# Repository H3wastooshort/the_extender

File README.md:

# The Extender
Modern phones suck in theor own unique way, don't they?
Hard-to-replace or -expand lithium cells, no expandable storage, and worst of all: no headphone jack!

This projects aims to fix some of those flaws by
combining a powerbank, USB hub, USB audio, and RP2040 IC into one very cursed PCB.

## Working Principle
5V power and battery charging is handled by an IP5310 powerbank IC.

The PCB connects to a phone via a low-profile 90° USB Type C cable (either [DIY](/cable) or [bought](https://de.aliexpress.com/item/1005005371248824.html)).
Once connected, the RP2040 turns on 5V power, then uses the FUSB302 to tell the phone via USB Power Delivery,
that it should keep charging while also switching into USB Data Host mode.

The phone then connects to the CH334F USB Hub IC, which in turn connects to several things:
 * a USB 3.0 socket for a USB Stick which is used to expand the internal storage,
 * the HS-100B USB audio IC, (only powered on when headphones are connected)
 * the RP2040 for HID volume and playback control aswell as FW Updates,
 * and an external USB 2.0 socket for whatever you desire.

## 3D-printable case
WIP

## schematic POIs

### HS-100B Audio IC
 * The Audio IC circuit is based on a low-resolution image of a reference design i found online.
 * 5V Power to the IC gets cut va a MOSFET when the headphones are disconnected. An RC circuit prevents loose plugs from causing issues. (Turns off about 1 second after unplugging)
 * The datasheet is quite sparse
 * The EEPROM data lines are connected to the RP2040, so that it can emulate the EEPROM in the future. This is not requred.

### IP5310 power-bank IC
 * I2C variant is unobtainium
 * MOSFET between VOUT and rest of system, so that power to phone and other components can be controlled
   even though VOUT can't.
 * if needed, a solder jumper can be cut and shottky diode put in place to prevent current flowing back into the IC
 * KEY pin connected to RP2040. might be needed, i don't know, should turn on when detecting a load
 * D+ and D- not connected because there is very little space. the CC lines should suffice

### CH334F
 * clock line can be grounded to use internal OSC, but this is discouraged in its datasheet.
   RP2040 is to provide a better clock once programmed.
 * 

### RP2040
 * main purpose is to communicate via USB C PD
 * might supply clock for hub
 * might be used to emulate EEPROMs for USB Hub and Audio

## more info

The [idea](/idea) directory has some partially outdated notes.

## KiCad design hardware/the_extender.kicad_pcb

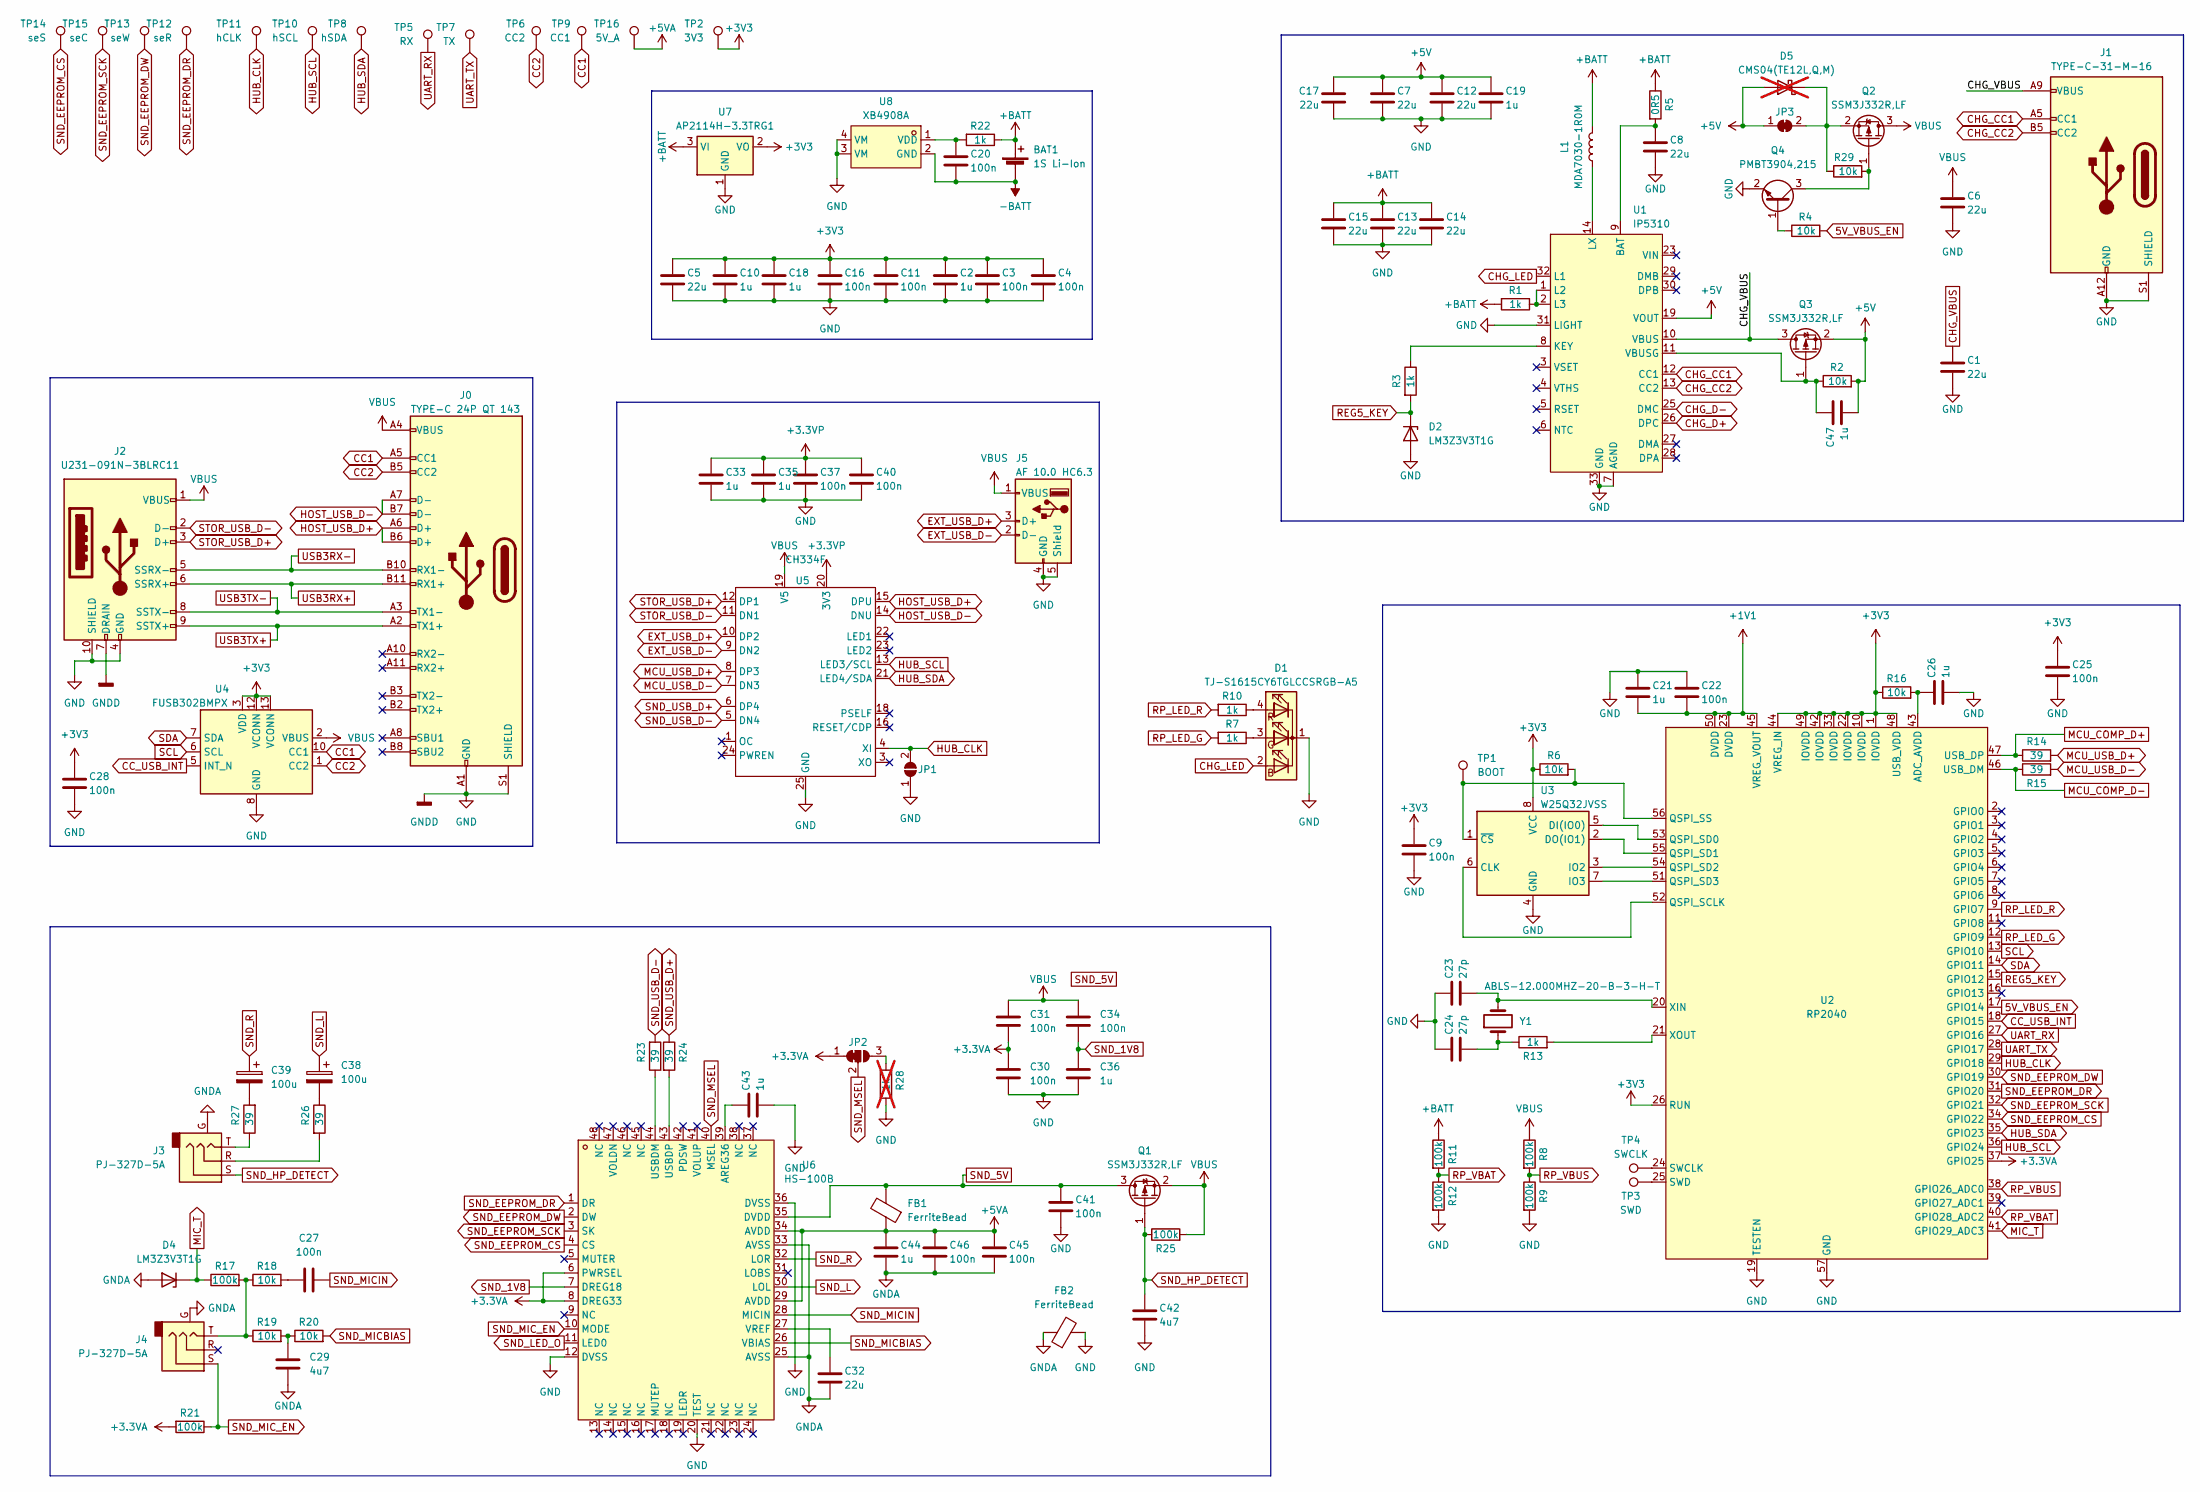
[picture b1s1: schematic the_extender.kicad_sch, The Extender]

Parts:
BAT1: 1S Li-Ion; PinHeader_1x02_P2.54mm_Vertical
C1, C5, C6, C7, C8, C12, C13, C14, C15, C17, C32: 22u; C_1206_3216Metric_Pad1.33x1.80mm_HandSolder; LCSC C12891
C2, C10, C18, C19, C21, C26, C33, C35, C36, C43, C44, C47: 1u; C_0805_2012Metric_Pad1.18x1.45mm_HandSolder; LCSC C116352
C3, C4, C9, C11, C16, C20, C22, C25, C27, C28, C30, C31, C34, C37, C40, C41, C45, C46: 100n; C_0805_2012Metric_Pad1.18x1.45mm_HandSolder; LCSC C1711
C23, C24: 27p; C_0805_2012Metric_Pad1.18x1.45mm_HandSolder; LCSC C525289
C29, C42: 4u7; C_0805_2012Metric_Pad1.18x1.45mm_HandSolder; LCSC C1779
C38, C39: 100u; C_1206_3216Metric_Pad1.33x1.80mm_HandSolder; LCSC C15008
D1: TJ-S1615CY6TGLCCSRGB-A5; LED-ARRAY-SMD_4P-L1.6-W1.5-BL-FD; LCSC C601684
D2, D4: LM3Z3V3T1G; D_SOD-323_HandSoldering; LCSC C46279
D5: CMS04(TE12L,Q,M); D_SOD-128; LCSC C603062; not fitted
FB1, FB2: FerriteBead; L_0805_2012Metric_Pad1.05x1.20mm_HandSolder; LCSC C394433
J0: TYPE-C 24P QT 143; TYPE-C-SMD_C9900025773; LCSC Part C5156605
J1: TYPE-C-31-M-16; LCSC C283541
J2: U231-091N-3BLRC11; USB-A-TH_XKB_U231-091N-XXX; LCSC Part C2880594
J3, J4: PJ-327D-5A; AUDIO-TH_PJ-327D-5A; LCSC Part C707229
J5: AF 10.0 HC6.3; USB-A-TH_AF-10.0-HC6.3; LCSC Part C456017
JP1: SolderJumper_2_Open; SolderJumper-2_P1.3mm_Open_TrianglePad1.0x1.5mm
JP2: SolderJumper_3_Bridged12; SolderJumper-3_P1.3mm_Bridged12_Pad1.0x1.5mm_NumberLabels
JP3: SolderJumper_2_Bridged; SolderJumper-2_P1.3mm_Bridged_Pad1.0x1.5mm
L1: MDA7030-1R0M; IND-SMD_L7.1-W6.6; LCSC Part C2847480
Q1, Q2, Q3: SSM3J332R,LF; SOT-23_Handsoldering; LCSC C146367
Q4: PMBT3904,215; SOT-23_Handsoldering; LCSC C8667
R1, R3, R7, R10, R13, R22: 1k; R_0805_2012Metric_Pad1.20x1.40mm_HandSolder; LCSC C110774
R2, R4, R6, R16, R18, R19, R20, R29: 10k; R_0805_2012Metric_Pad1.20x1.40mm_HandSolder; LCSC C217770
R5: 0R5; R_0805_2012Metric_Pad1.20x1.40mm_HandSolder; LCSC C218422
R8, R9, R11, R12, R17, R21, R25: 100k; R_0805_2012Metric_Pad1.20x1.40mm_HandSolder; LCSC C217765
R14, R15, R23, R24, R26, R27: 39; R_0805_2012Metric_Pad1.20x1.40mm_HandSolder; LCSC C2828722
R28: 1k; R_0805_2012Metric_Pad1.20x1.40mm_HandSolder; LCSC C110774; not fitted
TP1: BOOT; TestPoint_Pad_D2.0mm
TP2: 3V3; TestPoint_Pad_D2.0mm
TP3: SWD; TestPoint_Pad_D2.0mm
TP4: SWCLK; TestPoint_Pad_D2.0mm
TP5: RX; TestPoint_Pad_D1.0mm
TP6: CC2; TestPoint_Pad_D1.0mm
TP7: TX; TestPoint_Pad_D2.0mm
TP8: hSDA; TestPoint_Pad_D1.0mm
TP9: CC1; TestPoint_Pad_D1.0mm
TP10: hSCL; TestPoint_Pad_D1.0mm
TP11: hCLK; TestPoint_Pad_D1.0mm
TP12: seR; TestPoint_Pad_D2.0mm
TP13: seW; TestPoint_Pad_D2.0mm
TP14: seS; TestPoint_Pad_D2.0mm
TP15: seC; TestPoint_Pad_D2.0mm
TP16: 5V_A; TestPoint_Pad_D2.0mm
U1: IP5310; QFN-32_L5.0-W5.0-P0.50-BL-EP3.4; LCSC Part C191176
U2: RP2040; LQFN-56_L7.0-W7.0-P0.4-EP; LCSC Part C2040
U3: W25Q32JVSS; SOIC-8_5.23x5.23mm_P1.27mm; LCSC C179173
U4: FUSB302BMPX; WQFN-14-1EP_2.5x2.5mm_P0.5mm_EP1.45x1.45mm; LCSC Part C442699
U5: CH334F; QFN-24-1EP_4x4mm_P0.5mm_EP2.6x2.6mm; LCSC Part C5187527
U6: HS-100B; LQFP-48_7x7mm_P0.5mm; LCSC Part C371351
U7: AP2114H-3.3TRG1; SOT-223-3_TabPin2; LCSC C150716
U8: XB4908A; ESN-4_L2.8-W2.3-LS3.7-BL; LCSC Part C2998740
Y1: ABLS-12.000MHZ-20-B-3-H-T; Crystal_SMD_7050-2Pin_7.0x5.0mm_HandSoldering; LCSC C1985323

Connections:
5V_VBUS_EN: R4.2, U2.17 (GPIO14)
+1V1: C21.2, C22.2, U2.23 (DVDD), U2.45 (VREG_VOUT), U2.50 (DVDD)
+3.3VA: C30.2, C31.1, JP2.1 (A), R21.2, U2.37 (GPIO25), U6.6 (PWRSEL), U6.8 (DREG33)
+3.3VP: C33.1, C35.1, C37.1, C40.1, U5.20 (3V3)
+3V3: C2.1, C3.1, C4.1, C5.1, C9.1, C10.1, C11.1, C16.1, C18.1, C25.1, C28.1, R6.1, R16.1, TP2.1, U2.1 (IOVDD), U2.10 (IOVDD), U2.22 (IOVDD), U2.26 (RUN), U2.33 (IOVDD), U2.42 (IOVDD), U2.44 (VREG_IN), U2.48 (USB_VDD), U2.49 (IOVDD), U3.8 (VCC), U4.3 (VDD), U4.4 (VDD), U4.12 (VCONN), U4.13 (VCONN), U7.2 (VO)
+5V: C7.1, C12.1, C17.1, C19.1, C47.2, D5.2 (A), JP3.1 (A), Q3.2 (S), R2.2, U1.19 (VOUT), U1.20 (VOUT), U1.21 (VOUT), U1.22 (VOUT)
+5VA: C44.1, C45.1, C46.1, FB1.1, TP16.1, U6.29 (AVDD), U6.34 (AVDD)
+BATT: BAT1.1 (+), C13.1, C14.1, C15.1, L1.2, R1.2, R5.1, R11.1, R22.1, U7.3 (VI)
-BATT: BAT1.2 (-), C20.2, U8.2 (GND)
CC1: J0.A5 (CC1), TP9.1, U4.10 (CC1), U4.11 (CC1)
CC2: J0.B5 (CC2), TP6.1, U4.1 (CC2), U4.14 (CC2)
CC_USB_INT: U2.18 (GPIO15), U4.5 (INT_N)
CHG_CC1: J1.A5 (CC1), U1.12 (CC1)
CHG_CC2: J1.B5 (CC2), U1.13 (CC2)
CHG_D+: U1.26 (DPC)
CHG_D-: U1.25 (DMC)
CHG_LED: D1.2 (BA), U1.32 (L1)
CHG_VBUS: C1.1, J1.A9 (VBUS), J1.B9 (VBUS), Q3.3 (D), U1.10 (VBUS)
EXT_USB_D+: J5.3 (D+), U5.10 (DP2)
EXT_USB_D-: J5.2 (D-), U5.9 (DN2)
GND: C1.2, C2.2, C3.2, C4.2, C5.2, C6.2, C7.2, C8.2, C9.2, C10.2, C11.2, C12.2, C13.2, C14.2, C15.2, C16.2, C17.2, C18.2, C19.2, C21.1, C22.1, C23.1, C24.1, C25.2, C26.2, C28.2, C30.1, C33.2, C35.2, C36.1, C37.2, C40.2, C41.2, C42.2, C43.2, D1.1 (K), D2.2 (A), FB2.2, J0.A1 (GND), J0.A12 (GND), J0.B1 (GND), J0.B12 (GND), J0.S1 (SHIELD), J1.A12 (GND), J1.B12 (GND), J1.S1 (SHIELD), J2.4 (GND), J2.7 (DRAIN), J2.10 (SHIELD), J5.4 (GND), J5.5 (Shield), JP1.1 (A), Q4.2 (E), R9.2, R12.2, R28.1, U1.7 (AGND), U1.31 (LIGHT), U1.33 (GND), U2.19 (TESTEN), U2.57 (GND), U3.4 (GND), U4.8 (GND), U4.9 (GND), U4.15 (GND), U5.25 (GND), U6.12 (DVSS), U6.20 (TEST), U6.36 (DVSS), U7.1 (GND), U8.3 (VM), U8.4 (VM)
GNDA: C29.1, C32.2, C44.2, C45.2, C46.2, D4.2 (A), FB2.1, J3.G, J4.G, U6.25 (AVSS), U6.33 (AVSS)
HOST_USB_D+: J0.A6 (D+), J0.B6 (D+), U5.15 (DPU)
HOST_USB_D-: J0.A7 (D-), J0.B7 (D-), U5.14 (DNU)
HUB_CLK: JP1.2 (B), TP11.1, U2.29 (GPIO18), U5.4 (XI)
HUB_SCL: TP10.1, U2.36 (GPIO24), U5.13 (LED3/SCL)
HUB_SDA: TP8.1, U2.35 (GPIO23), U5.21 (LED4/SDA)
MCU_COMP_D+: R14.1, U2.47 (USB_DP)
MCU_COMP_D-: R15.1, U2.46 (USB_DM)
MCU_USB_D+: R14.2, U5.8 (DP3)
MCU_USB_D-: R15.2, U5.7 (DN3)
MIC_T: D4.1 (K), R17.1, U2.41 (GPIO29_ADC3)
unnamed: C24.2, R13.1, Y1.1
unnamed: C27.1, R18.2
unnamed: C29.2, R19.2, R20.1
unnamed: C38.2, R26.1
unnamed: C39.2, R27.2
unnamed: D1.3 (GA), R7.1
unnamed: D1.4 (RA), R10.1
unnamed: D5.1 (K), JP3.2 (B), Q2.2 (S), R29.1
unnamed: J3.R, R26.2
unnamed: J3.T, R27.1
unnamed: J4.T, R17.2, R18.1, R19.1
unnamed: JP2.3 (B), R28.2
unnamed: L1.1, U1.14 (LX), U1.15 (LX), U1.16 (LX), U1.17 (LX), U1.18 (LX)
unnamed: Q2.1 (G), Q4.3 (C), R29.2
unnamed: C47.1, Q3.1 (G), R2.1, U1.11 (VBUSG)
unnamed: Q4.1 (B), R4.1
unnamed: C8.1, R5.2, U1.9 (BAT)
unnamed: R3.1, U1.8 (KEY)
unnamed: R1.1, U1.1 (L2), U1.2 (L3)
unnamed: C26.1, R16.2, U2.43 (ADC_AVDD)
unnamed: U2.52 (QSPI_SCLK), U3.6 (CLK)
unnamed: U2.53 (QSPI_SD0), U3.5 (DI(IO0))
unnamed: U2.55 (QSPI_SD1), U3.2 (DO(IO1))
unnamed: U2.54 (QSPI_SD2), U3.3 (IO2)
unnamed: U2.51 (QSPI_SD3), U3.7 (IO3)
unnamed: R6.2, TP1.1, U2.56 (QSPI_SS), U3.1 (~CS)
unnamed: TP4.1, U2.24 (SWCLK)
unnamed: TP3.1, U2.25 (SWD)
unnamed: C23.2, U2.20 (XIN), Y1.2
unnamed: R13.2, U2.21 (XOUT)
unnamed: C43.1, U6.39 (AREG36)
unnamed: R23.1, U6.44 (USBDM)
unnamed: R24.2, U6.43 (USBDP)
unnamed: C32.1, U6.27 (VREF)
unnamed: C20.1, R22.2, U8.1 (VDD)
REG5_KEY: D2.1 (K), R3.2, U2.15 (GPIO12)
RP_LED_G: R7.2, U2.12 (GPIO9)
RP_LED_R: R10.2, U2.9 (GPIO7)
RP_VBAT: R11.2, R12.1, U2.40 (GPIO28_ADC2)
RP_VBUS: R8.2, R9.1, U2.38 (GPIO26_ADC0)
SCL: U2.13 (GPIO10), U4.6 (SCL)
SDA: U2.14 (GPIO11), U4.7 (SDA)
SND_1V8: C34.1, C36.2, U6.7 (DREG18)
SND_5V: C41.1, FB1.2, Q1.3 (D), U6.35 (DVDD)
SND_EEPROM_CS: TP14.1, U2.34 (GPIO22), U6.4 (CS)
SND_EEPROM_DR: TP12.1, U2.31 (GPIO20), U6.1 (DR)
SND_EEPROM_DW: TP13.1, U2.30 (GPIO19), U6.2 (DW)
SND_EEPROM_SCK: TP15.1, U2.32 (GPIO21), U6.3 (SK)
SND_HP_DETECT: C42.1, J3.S, Q1.1 (G), R25.1
SND_L: C38.1, U6.30 (LOL)
SND_LED_O: U6.11 (LED0)
SND_MICBIAS: R20.2, U6.26 (VBIAS)
SND_MICIN: C27.2, U6.28 (MICIN)
SND_MIC_EN: J4.S, R21.1, U6.10 (MODE)
SND_MSEL: JP2.2 (C), U6.40 (MSEL)
SND_R: C39.1, U6.32 (LOR)
SND_USB_D+: R24.1, U5.6 (DP4)
SND_USB_D-: R23.2, U5.5 (DN4)
STOR_USB_D+: J2.3 (D+), U5.12 (DP1)
STOR_USB_D-: J2.2 (D-), U5.11 (DN1)
UART_RX: TP5.1, U2.27 (GPIO16)
UART_TX: TP7.1, U2.28 (GPIO17)
USB3RX+: J0.B11 (RX1+), J2.6 (SSRX+)
USB3RX-: J0.B10 (RX1-), J2.5 (SSRX-)
USB3TX+: J0.A2 (TX1+), J2.9 (SSTX+)
USB3TX-: J0.A3 (TX1-), J2.8 (SSTX-)
VBUS: C6.1, C31.2, C34.2, J0.A4 (VBUS), J0.A9 (VBUS), J0.B4 (VBUS), J0.B9 (VBUS), J2.1 (VBUS), J5.1 (VBUS), Q1.2 (S), Q2.3 (D), R8.1, R25.2, U4.2 (VBUS), U5.19 (V5)

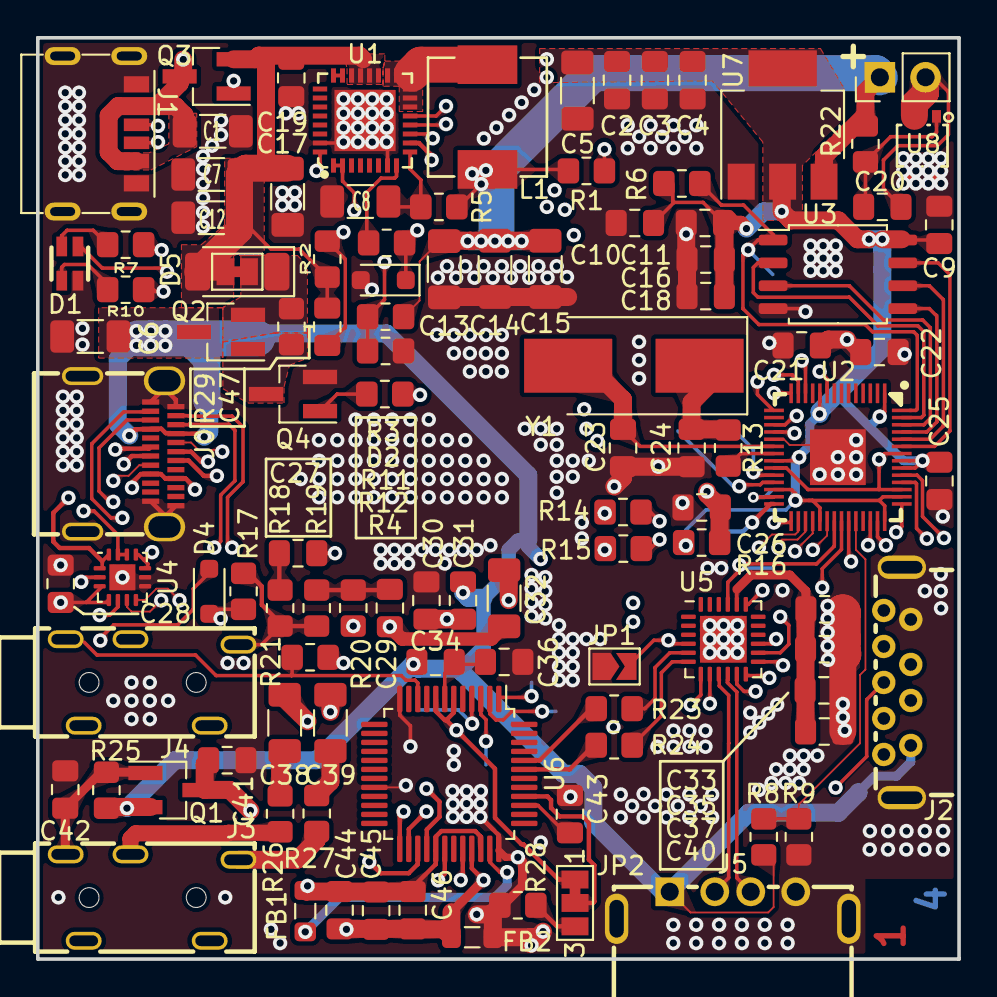
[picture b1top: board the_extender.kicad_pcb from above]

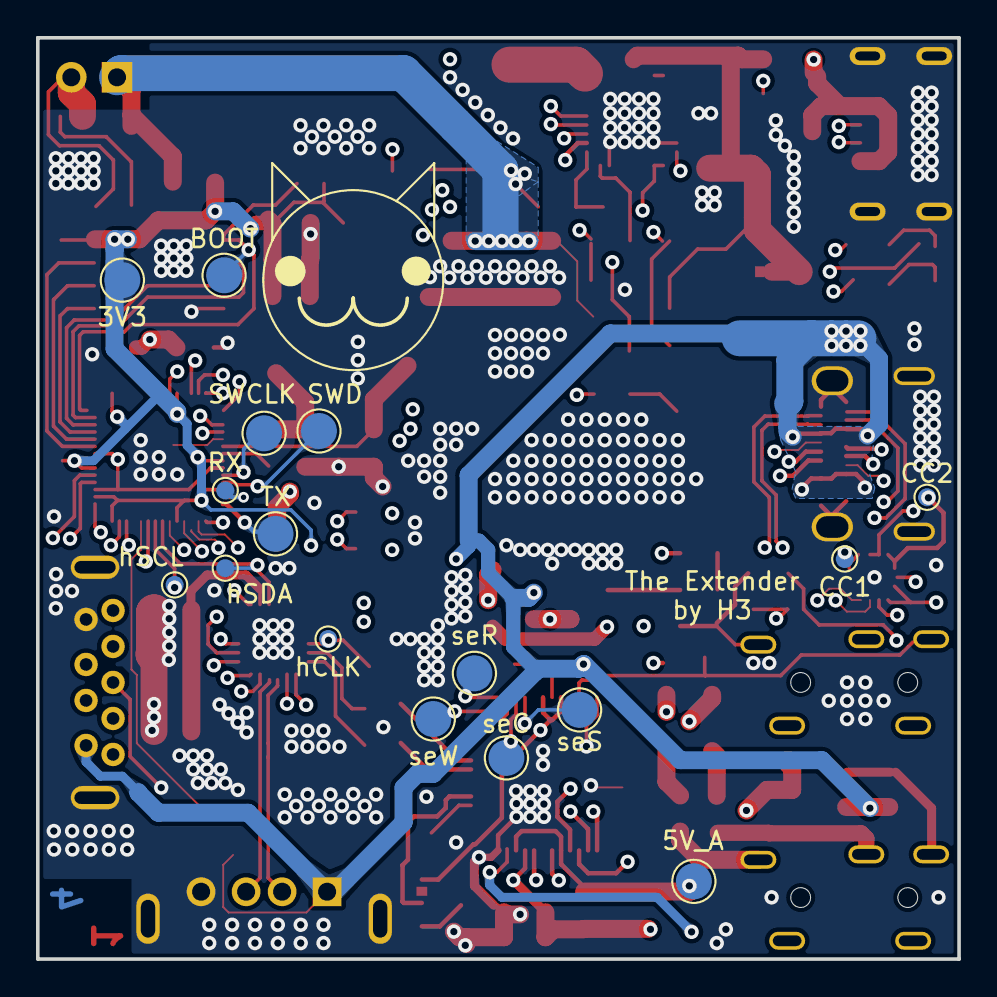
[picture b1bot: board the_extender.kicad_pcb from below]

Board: 4 copper layers, 51.2 x 51.2 mm, 122 parts (16 on the bottom side), 96 nets.

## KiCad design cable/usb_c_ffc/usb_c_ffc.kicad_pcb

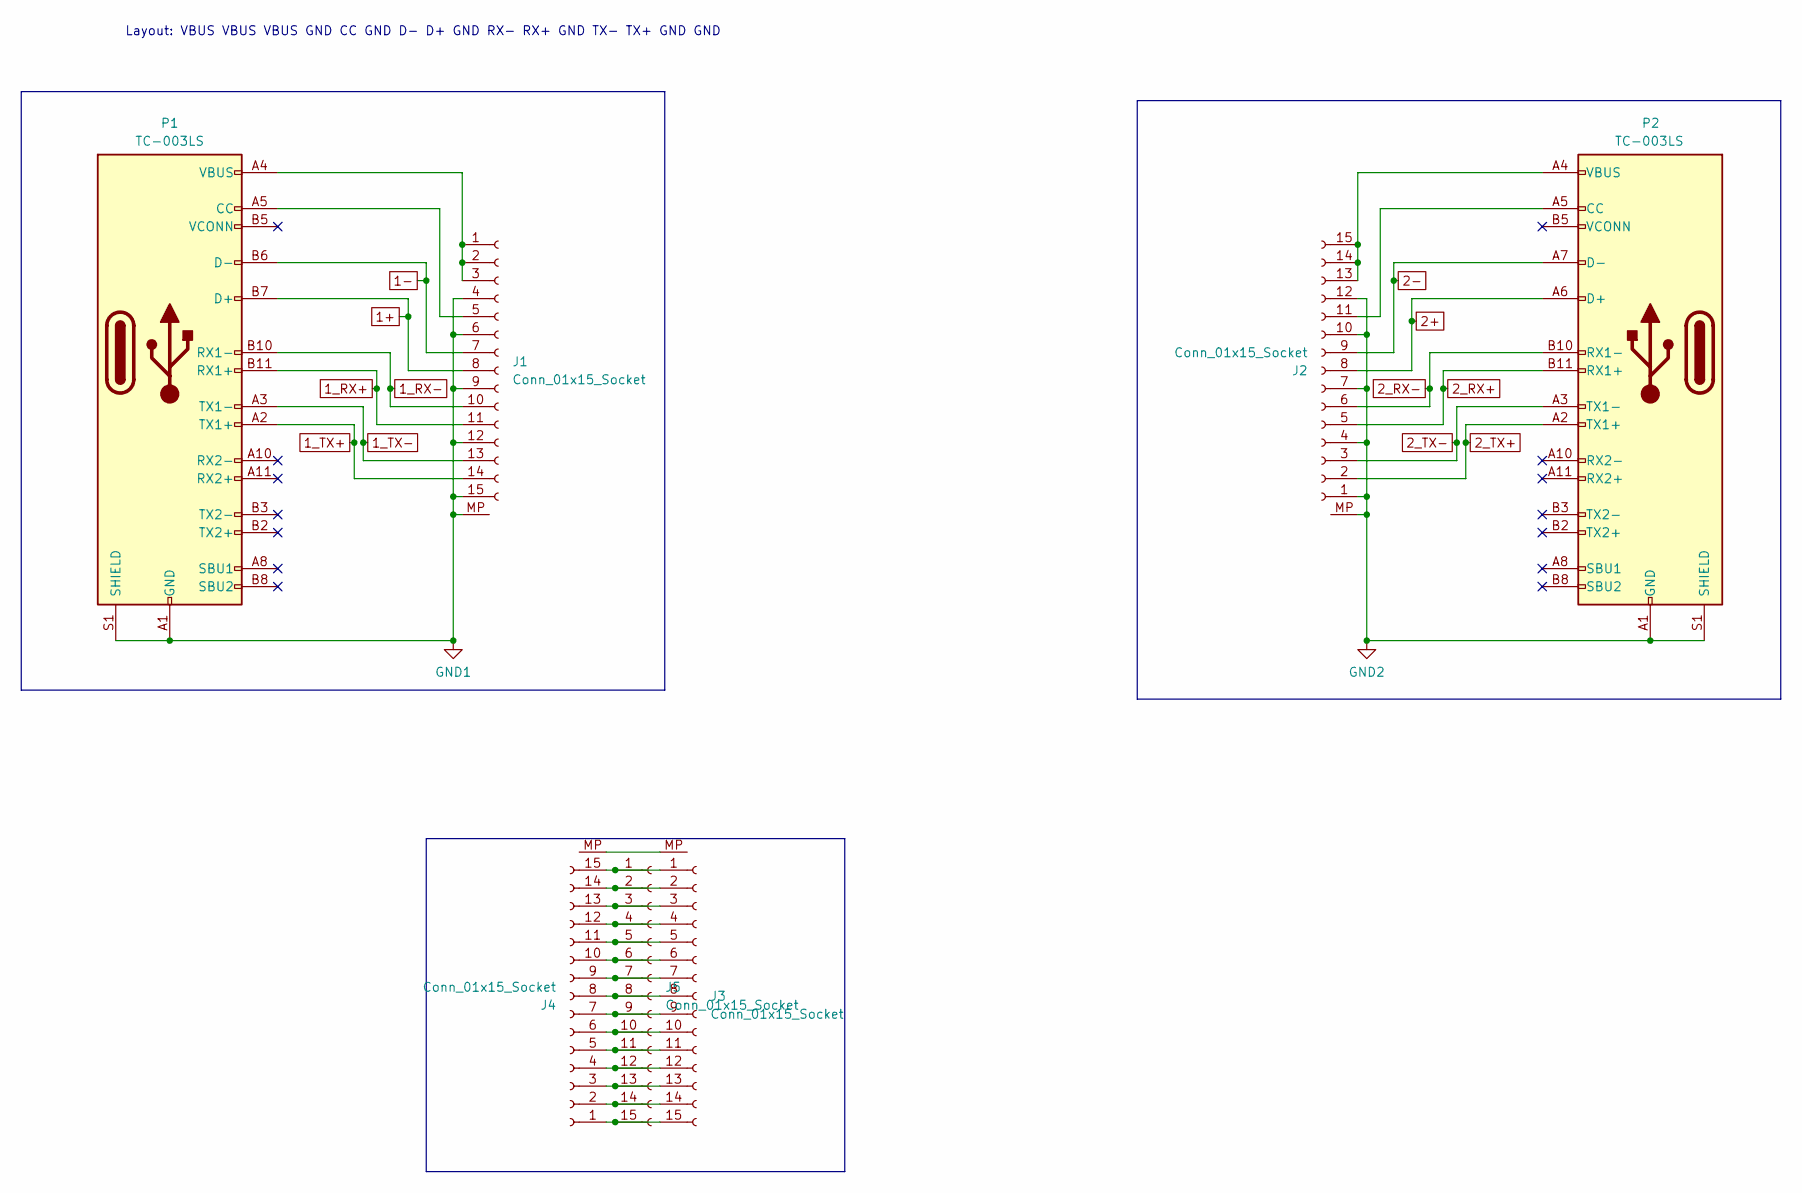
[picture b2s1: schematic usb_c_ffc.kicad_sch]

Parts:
J1, J2, J3, J4: Conn_01x15_Socket; Molex_200528-0150_1x15-1MP_P1.00mm_Horizontal
J5: Conn_01x15_Socket; PinHeader_1x15_P2.54mm_Vertical
P1, P2: TC-003LS

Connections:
1+: J1.8, P1.B7 (D+)
1-: J1.7, P1.B6 (D-)
1_RX+: J1.11, P1.B11 (RX1+)
1_RX-: J1.10, P1.B10 (RX1-)
1_TX+: J1.14, P1.A2 (TX1+)
1_TX-: J1.13, P1.A3 (TX1-)
2+: J2.8, P2.A6 (D+)
2-: J2.9, P2.A7 (D-)
2_RX+: J2.5, P2.B11 (RX1+)
2_RX-: J2.6, P2.B10 (RX1-)
2_TX+: J2.2, P2.A2 (TX1+)
2_TX-: J2.3, P2.A3 (TX1-)
GND1: J1.4, J1.6, J1.9, J1.12, J1.15, J1.MP, P1.A1 (GND), P1.A12 (GND), P1.B1 (GND), P1.B12 (GND), P1.S1 (SHIELD)
GND2: J2.1, J2.4, J2.7, J2.10, J2.12, J2.MP, P2.A1 (GND), P2.A12 (GND), P2.B1 (GND), P2.B12 (GND), P2.S1 (SHIELD)
unnamed: J1.1, J1.2, J1.3, P1.A4 (VBUS), P1.A9 (VBUS), P1.B4 (VBUS), P1.B9 (VBUS)
unnamed: J1.5, P1.A5 (CC)
unnamed: J2.11, P2.A5 (CC)
unnamed: J2.13, J2.14, J2.15, P2.A4 (VBUS), P2.A9 (VBUS), P2.B4 (VBUS), P2.B9 (VBUS)
unnamed: J3.MP, J4.MP
unnamed: J3.1, J4.15, J5.1
unnamed: J3.2, J4.14, J5.2
unnamed: J3.3, J4.13, J5.3
unnamed: J3.4, J4.12, J5.4
unnamed: J3.5, J4.11, J5.5
unnamed: J3.6, J4.10, J5.6
unnamed: J3.7, J4.9, J5.7
unnamed: J3.8, J4.8, J5.8
unnamed: J3.9, J4.7, J5.9
unnamed: J3.10, J4.6, J5.10
unnamed: J3.11, J4.5, J5.11
unnamed: J3.12, J4.4, J5.12
unnamed: J3.13, J4.3, J5.13
unnamed: J3.14, J4.2, J5.14
unnamed: J3.15, J4.1, J5.15

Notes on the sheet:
Layout: VBUS VBUS VBUS GND CC GND D- D+ GND RX- RX+ GND TX- TX+ GND GND

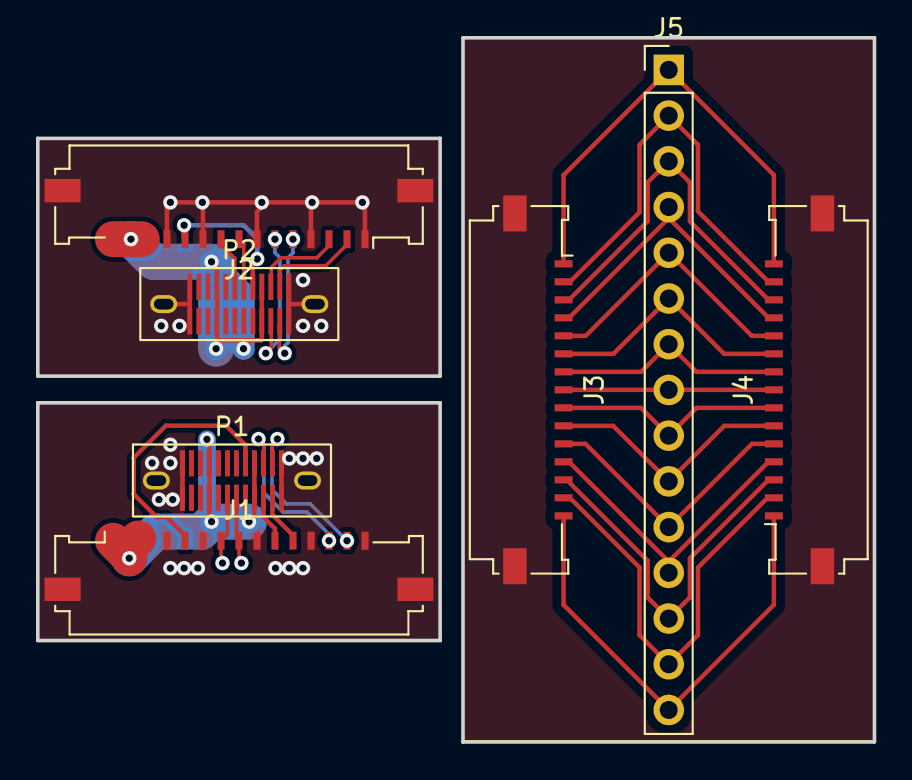
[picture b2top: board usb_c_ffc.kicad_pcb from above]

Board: 2 copper layers, 46.5 x 39.1 mm, 7 parts (0 on the bottom side), 34 nets.

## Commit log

2023-12-17 worked on schematic
2023-12-17 some more caps n stuff
2023-12-20 did things
2023-12-21 did things, tried to arrange components
2023-12-21 trying to layout board
2023-12-22 got most stuff stuffed onto the PCB
2023-12-22 flip layers so power is routed on heavier traces
2023-12-22 done some more stuff
2023-12-23 i might have finished routing signals
2023-12-23 ground planes in
2023-12-23 added some missing connections
2023-12-23 fix bugs
2023-12-23 use default footprints
2023-12-23 add missing trace, fix bugs
2023-12-25 added even more connections i forgot
2023-12-25 stuff
2023-12-25 automatic cleanup
2023-12-25 manual cleanup
2023-12-25 better groundplane for pb chip
2023-12-25 improve groundplanes
2023-12-26 add lcsc mappings
2023-12-26 3d models
2023-12-26 DRC stuff
2023-12-27 reread IP5310 datasheet, better groundplanes, other
2023-12-27 actually fix U6 footprint
2023-12-28 fix clearances
2023-12-28 more clearance and ground stuff
2023-12-28 auto cleanup
2023-12-28 part of 4ac6dc7472c68df24555d1d21356125b5eaefc59
2023-12-28 dont need VBUS on FUSB302
    that just kills them sometimes
2023-12-28 notes
2023-12-28 rp2040 boot TP
2023-12-28 update to kicad 7
2023-12-28 stuff
    clearances, remove unnesaccary components, etc
2023-12-28 program flow
2023-12-28 added layer indicator
2023-12-28 switch to new connector, part a
2023-12-28 new connector, part 2
2023-12-28 geographical reannotate
2023-12-29 added CC test pads
2023-12-30 debug TX pad
2023-12-30 usb c stuff idea
2023-12-30 todo
2023-12-30 now i know
2023-12-31 Imported code from @CRImier /AltmodeFriend
    https://github.com/CRImier/AltmodeFriend/blob/main/main.py
2023-12-31 strip sink stuff
2023-12-31 idk if that works
2023-12-31 take out more sink stuff
    this is nice code, but the extender should never be a sink and i want to keep this as short as possible. sorry
2023-12-31 sketch
2023-12-31 freq
2024-01-01 added USB C flat-flex cable adapters
2024-01-02 giving up on eeprom emulation, not enough board space
2024-01-03 cable pcb panel
2024-01-03 better HP detection
2024-01-04 applied changes to PCB
2024-01-04 add EEPROM emulation back
2024-01-04 amend todo
2024-01-04 silkscreen overlap, geo reannotate, teardrops
2024-01-04 oops, forgot to refill zones
2024-01-04 move cable files
2024-01-04 protect RP2040 from 3V6
2024-01-05 switching to IP5306, step 1: schematic
2024-01-05 bruh
2024-01-05 oh yeah, the 5k1 resistors
2024-01-05 switching to IP5306, step 2: PCB
2024-01-05 had to move the IC a little
2024-01-05 fixup silkscreen, voltage limits, etc
2024-01-05 fix U6 being detected as "additional footprint"
2024-01-07 fix me fucking up footprints
2024-01-07 use mousebites on cable instead
2024-01-07 ah whatever
    i will just go with 3 seperate PCBs. its actually cheaper that way
2024-01-07 split
2024-01-07 add debounce circuit
2024-01-07 gitignore
2024-01-07 teardrops
2024-01-10 finalizing design
2024-01-10 still not quite done
2024-01-11 reconnect VBUS to FUSB302
    i think its needed for the pullups
2024-01-11 update LCSC parts
2024-01-11 add bom conversion script
2024-01-11 switch 3v3 footprint, fixup stuff
2024-01-11 forgot to change id
2024-01-13 trying to do a customizable case in scad
2024-01-17 switch to cheaper and smaller usb hub, part 1
2024-01-17 switch usb hub, part 2: PCB
2024-01-17 board optimizations
2024-01-17 small fixes
2024-01-17 Switch to linear LDO Regulator to decrease cost
    might also improve ADC accuracy...
2024-01-17 slightly improved thermal fill
2024-01-17 removed back s.mask from some in-pad vias
2024-01-17 oops
2024-01-17 auto-cleanup
2024-01-17 oh, this belongs to an earlier commit
2024-01-18 update LCSC parts
    i always forgot to update the schematic :facepalm:
2024-01-18 [bom script] count components
2024-01-18 fix lcsc parts
2024-01-18 fix bom excludes
2024-01-18 change inductor and fix things
2024-01-18 geo reannotate
2024-01-21 fix some more in-pad-vias
2024-01-26 space comonents out more in audio section
2024-01-26 add teardrops
2024-01-26 forgot to refill zones. oops
2024-01-26 fix testpad labels
2024-01-26 fix LCSC part numbers
2024-01-26 ground area
2024-01-26 lcsc ids
2024-02-09 added headphone plug-in detection, other stuff
2024-02-09 fix USB3 footprint
2024-02-09 silkscreen slightly more readable
2024-02-09 silkscreen
2024-02-15 add 5V solderjumper
2024-02-15 remove teardrops again
2024-02-15 add diode mosfet
2024-02-15 ok, just a regular diode then...
2024-02-15 fix DRC errors
2024-02-15 move silk txt
2024-02-15 switche diode FP, shuffle silk around
2024-02-15 more silk stuff
2024-02-15 auto-cleanup and taerdrops
2024-02-16 move USB3 cable to seperate folder
2024-02-16 added nice little USB2 cable variant
2024-02-16 hide too small silkscreen text
2024-02-16 change routing
2024-02-17 switching back to IP5310, step 1: schematic
    Switching back to IP5310 with different 5V enable circuit
    This has several advantages:
    * being able to output power via the charging port
    * being sure the 5V power will be able to be switched off
    * 3A-capable supply
    Disadvantage:
2024-02-17 npn selection
2024-02-17 rm teardrops
2024-02-17 kinda did it
2024-02-17 add way to measure VBUS
2024-02-17 silk slightly less horrible
2024-02-18 silkscreen schubsen
2024-02-18 add Li-Ion protection circuit
2024-02-18 cell protection fixes
2024-02-18 reinforce BATT- with solder, small fixes
2024-02-18 lcsc
2024-02-18 change RGB LED
    old one was out of stock
2024-02-18 led 3d model
2024-02-22 improved thermal areas, trace routing, other
2024-02-22 gnd fix
2024-02-22 auto clean and fix teardrops
2024-02-22 i forgot to rebuild zones
2024-02-22 stop DRC from complaining
2024-02-22 why did the LCSC part numbers not transfer?
2024-02-22 slight routing changes
2024-03-01 add more TPs, opem SolderJumper
2024-03-01 move TPs
2024-03-01 fix DRC error
2024-03-01 refresh teardrops
2024-03-01 Revert "Merge branch 'main' of https://github.com/H3wastooshort/the_extender"
    This reverts commit db196a6756d0956c3d1d8ec495d7e3985efbbc7b, reversing
    changes made to 4fcd2dbd9a370267836c4c164a7f38c8495f449e.
2024-03-01 Revert "stuff"
    This reverts commit 4fcd2dbd9a370267836c4c164a7f38c8495f449e.
2024-03-15 add and update docs
2024-03-15 update docs
2024-03-15 fix diagram font
2024-03-16 add schematic POIs
2024-03-16 rearrange schematic
2024-03-16 rearrange schematic a bit more
2024-03-17 try using CI
2024-03-17 correct revision
2024-03-17 fix CI
2024-03-17 allow manual triggering
2024-03-17 upgrade to checkout@v4
2024-05-05 use same doc generation wf from BikeUSBv2
2024-05-05 name
2024-05-05 use auto-generated images
2024-05-05 fix DRC complaint
2024-05-23 try fixing GHA-rendered images
2024-05-23 2nd attempt
2024-05-23 3rd attempt
2024-05-23 also render rotating PCB
2024-05-23 add PCB gif to readme
2024-05-23 another attempt
2024-05-23 Revert "another attempt"
    This reverts commit 288c0018775d544f383a750716c72db4144e6e0d.
